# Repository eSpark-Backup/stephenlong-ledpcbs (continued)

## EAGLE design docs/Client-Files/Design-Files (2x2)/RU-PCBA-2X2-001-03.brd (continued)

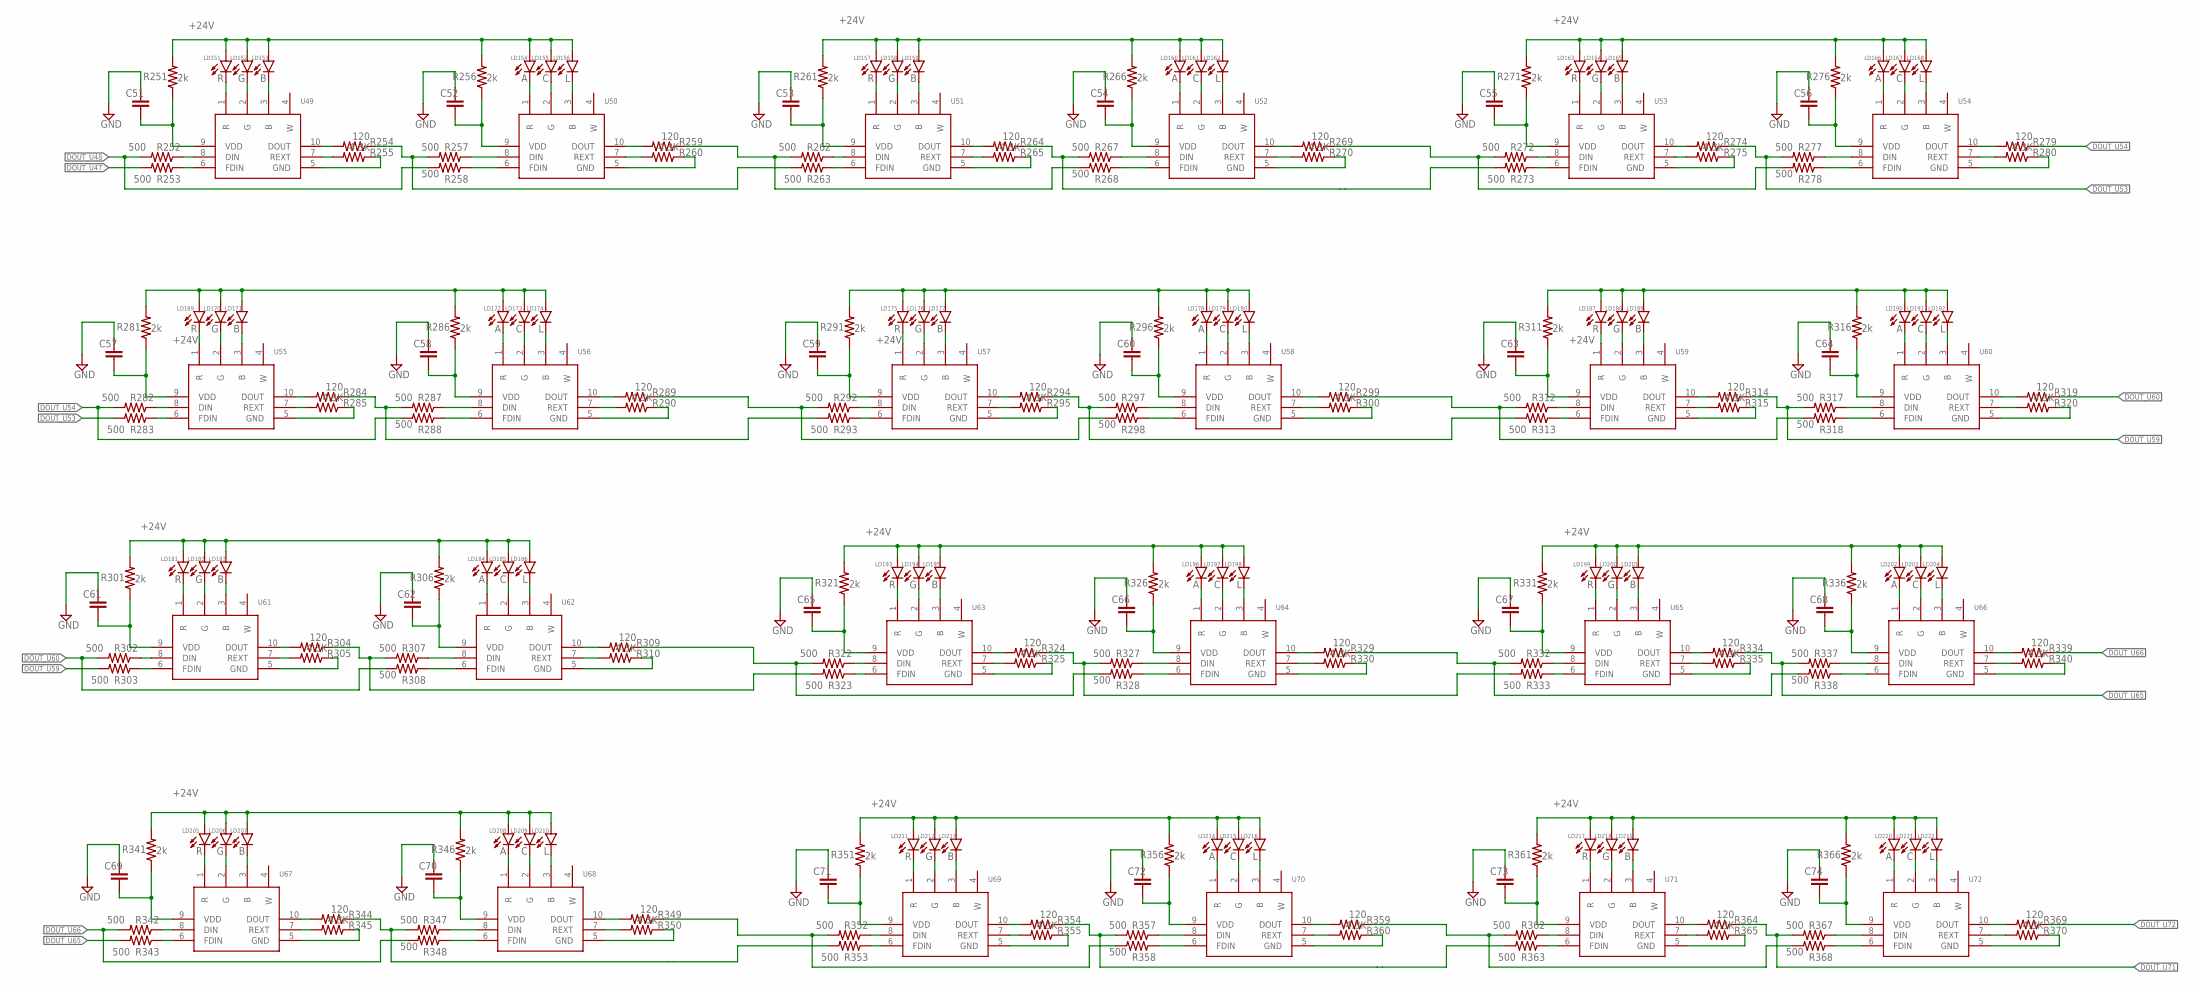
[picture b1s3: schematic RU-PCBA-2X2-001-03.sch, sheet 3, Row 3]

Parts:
C51, C52, C53, C54, C55, C56, C57, C58, C59, C60, C61, C62, C63, C64, C65, C66, C67, C68, C69, C70, C71, C72, C73, C74: C-EUC1206; C1206; MPN C_104
LD151, LD157, LD163, LD169, LD175, LD181, LD187, LD193, LD199, LD205, LD211, LD217: R; 5050LED; MPN R_5050
LD152, LD158, LD164, LD170, LD176, LD182, LD188, LD194, LD200, LD206, LD212, LD218: G; 5050LED; MPN G_5050
LD153, LD159, LD165, LD171, LD177, LD183, LD189, LD195, LD201, LD207, LD213, LD219: B; 5050LED; MPN B_5050
LD154, LD160, LD166, LD172, LD178, LD184, LD190, LD196, LD202, LD208, LD214, LD220: A; 5050LED; MPN A_5050
LD155, LD161, LD167, LD173, LD179, LD185, LD191, LD197, LD203, LD209, LD215, LD221: C; 5050LED; MPN C_5050
LD156, LD162, LD168, LD174, LD180, LD186, LD192, LD198, LD204, LD210, LD216, LD222: L; 5050LED; MPN L_5050
R251, R256, R261, R266, R271, R276, R281, R286, R291, R296, R301, R306, R311, R316, R321, R326, R331, R336, R341, R346, R351, R356, R361, R366: 2k; R1206; MPN R_VDD
R252, R253, R257, R258, R262, R263, R267, R268, R272, R273, R277, R278, R282, R283, R287, R288, R292, R293, R297, R298, R302, R303, R307, R308, R312, R313, R317, R318, R322, R323, R327, R328, R332, R333, R337, R338, R342, R343, R347, R348, R352, R353, R357, R358, R362, R363, R367, R368: 500; R0805; MPN R_500
R254, R259, R264, R269, R274, R279, R284, R289, R294, R299, R304, R309, R314, R319, R324, R329, R334, R339, R344, R349, R354, R359, R364, R369: 120; R0805; MPN R_120
R255, R260, R265, R270, R275, R280, R285, R290, R295, R300, R305, R310, R315, R320, R325, R330, R335, R340, R345, R350, R355, R360, R365, R370: 4.3K; R0805; MPN R_EXT
U49, U50, U51, U52, U53, U54, U55, U56, U57, U58, U59, U60, U61, U62, U63, U64, U65, U66, U67, U68, U69, U70, U71, U72: UCS7604; SOP100P600X175-10N; MPN UCS7604

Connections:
+24V: LD151.A, LD152.A, LD153.A, LD154.A, LD155.A, LD156.A, LD157.A, LD158.A, LD159.A, LD160.A, LD161.A, LD162.A, LD163.A, LD164.A, LD165.A, LD166.A, LD167.A, LD168.A, LD169.A, LD170.A, LD171.A, LD172.A, LD173.A, LD174.A, LD175.A, LD176.A, LD177.A, LD178.A, LD179.A, LD180.A, LD181.A, LD182.A, LD183.A, LD184.A, LD185.A, LD186.A, LD187.A, LD188.A, LD189.A, LD190.A, LD191.A, LD192.A, LD193.A, LD194.A, LD195.A, LD196.A, LD197.A, LD198.A, LD199.A, LD200.A, LD201.A, LD202.A, LD203.A, LD204.A, LD205.A, LD206.A, LD207.A, LD208.A, LD209.A, LD210.A, LD211.A, LD212.A, LD213.A, LD214.A, LD215.A, LD216.A, LD217.A, LD218.A, LD219.A, LD220.A, LD221.A, LD222.A, R251.2, R256.2, R261.2, R266.2, R271.2, R276.2, R281.2, R286.2, R291.2, R296.2, R301.2, R306.2, R311.2, R316.2, R321.2, R326.2, R331.2, R336.2, R341.2, R346.2, R351.2, R356.2, R361.2, R366.2; also elsewhere on the board
DOUT_U47: R253.2; also elsewhere on the board
DOUT_U48: R252.2, R258.2; also elsewhere on the board
DOUT_U53: R274.1, R277.2, R283.2
DOUT_U54: R279.1, R282.2, R288.2
DOUT_U59: R303.2, R314.1, R317.2
DOUT_U60: R302.2, R308.2, R319.1
DOUT_U65: R334.1, R337.2, R343.2
DOUT_U66: R339.1, R342.2, R348.2
DOUT_U71: R364.1, R367.2; also elsewhere on the board
DOUT_U72: R369.1; also elsewhere on the board
GND: C51.2, C52.2, C53.2, C54.2, C55.2, C56.2, C57.2, C58.2, C59.2, C60.2, C61.2, C62.2, C63.2, C64.2, C65.2, C66.2, C67.2, C68.2, C69.2, C70.2, C71.2, C72.2, C73.2, C74.2, R255.1, R260.1, R265.1, R270.1, R275.1, R280.1, R285.1, R290.1, R295.1, R300.1, R305.1, R310.1, R315.1, R320.1, R325.1, R330.1, R335.1, R340.1, R345.1, R350.1, R355.1, R360.1, R365.1, R370.1, U49.5 (GND), U50.5 (GND), U51.5 (GND), U52.5 (GND), U53.5 (GND), U54.5 (GND), U55.5 (GND), U56.5 (GND), U57.5 (GND), U58.5 (GND), U59.5 (GND), U60.5 (GND), U61.5 (GND), U62.5 (GND), U63.5 (GND), U64.5 (GND), U65.5 (GND), U66.5 (GND), U67.5 (GND), U68.5 (GND), U69.5 (GND), U70.5 (GND), U71.5 (GND), U72.5 (GND); also elsewhere on the board
unnamed: C51.1, R251.1, U49.9 (VDD)
unnamed: LD151.K (C), U49.1 (R)
unnamed: LD152.K (C), U49.2 (G)
unnamed: LD153.K (C), U49.3 (B)
unnamed: R252.1, U49.8 (DIN)
unnamed: R253.1, U49.6 (FDIN)
unnamed: R254.2, U49.10 (DOUT)
unnamed: R255.2, U49.7 (REXT)
unnamed: LD154.K (C), U50.1 (R)
unnamed: LD155.K (C), U50.2 (G)
unnamed: LD156.K (C), U50.3 (B)
unnamed: C52.1, R256.1, U50.9 (VDD)
unnamed: R257.1, U50.8 (DIN)
unnamed: R258.1, U50.6 (FDIN)
unnamed: R259.2, U50.10 (DOUT)
unnamed: R260.2, U50.7 (REXT)
unnamed: R259.1, R262.2, R268.2
unnamed: C53.1, R261.1, U51.9 (VDD)
unnamed: LD157.K (C), U51.1 (R)
unnamed: LD158.K (C), U51.2 (G)
unnamed: LD159.K (C), U51.3 (B)
unnamed: R262.1, U51.8 (DIN)
unnamed: R263.1, U51.6 (FDIN)
unnamed: R264.2, U51.10 (DOUT)
unnamed: R265.2, U51.7 (REXT)
unnamed: LD160.K (C), U52.1 (R)
unnamed: LD161.K (C), U52.2 (G)
unnamed: LD162.K (C), U52.3 (B)
unnamed: C54.1, R266.1, U52.9 (VDD)
unnamed: R267.1, U52.8 (DIN)
unnamed: R268.1, U52.6 (FDIN)
unnamed: R254.1, R257.2, R263.2
unnamed: R269.2, U52.10 (DOUT)
unnamed: R270.2, U52.7 (REXT)
unnamed: R269.1, R272.2, R278.2
unnamed: C55.1, R271.1, U53.9 (VDD)
unnamed: LD163.K (C), U53.1 (R)
unnamed: LD164.K (C), U53.2 (G)
unnamed: LD165.K (C), U53.3 (B)
unnamed: R272.1, U53.8 (DIN)
unnamed: R273.1, U53.6 (FDIN)
unnamed: R274.2, U53.10 (DOUT)
unnamed: R275.2, U53.7 (REXT)
unnamed: LD166.K (C), U54.1 (R)
unnamed: LD167.K (C), U54.2 (G)
unnamed: LD168.K (C), U54.3 (B)
unnamed: C56.1, R276.1, U54.9 (VDD)
unnamed: R277.1, U54.8 (DIN)
unnamed: R278.1, U54.6 (FDIN)
unnamed: R264.1, R267.2, R273.2
unnamed: R279.2, U54.10 (DOUT)
unnamed: R280.2, U54.7 (REXT)
unnamed: C57.1, R281.1, U55.9 (VDD)
unnamed: LD169.K (C), U55.1 (R)
unnamed: LD170.K (C), U55.2 (G)
unnamed: LD171.K (C), U55.3 (B)
unnamed: R282.1, U55.8 (DIN)
unnamed: R283.1, U55.6 (FDIN)
unnamed: R284.2, U55.10 (DOUT)
unnamed: R285.2, U55.7 (REXT)
unnamed: LD172.K (C), U56.1 (R)
unnamed: LD173.K (C), U56.2 (G)
unnamed: LD174.K (C), U56.3 (B)
unnamed: C58.1, R286.1, U56.9 (VDD)
unnamed: R287.1, U56.8 (DIN)
unnamed: R284.1, R287.2, R293.2
unnamed: R288.1, U56.6 (FDIN)
unnamed: R289.2, U56.10 (DOUT)
unnamed: R290.2, U56.7 (REXT)
unnamed: R289.1, R292.2, R298.2
unnamed: C59.1, R291.1, U57.9 (VDD)
unnamed: LD175.K (C), U57.1 (R)
unnamed: LD176.K (C), U57.2 (G)
unnamed: LD177.K (C), U57.3 (B)
unnamed: R292.1, U57.8 (DIN)
unnamed: R293.1, U57.6 (FDIN)
unnamed: R294.2, U57.10 (DOUT)
unnamed: R295.2, U57.7 (REXT)
unnamed: LD178.K (C), U58.1 (R)
unnamed: LD179.K (C), U58.2 (G)
unnamed: LD180.K (C), U58.3 (B)
unnamed: C60.1, R296.1, U58.9 (VDD)
unnamed: R297.1, U58.8 (DIN)
unnamed: R294.1, R297.2, R313.2
unnamed: R298.1, U58.6 (FDIN)
unnamed: R299.2, U58.10 (DOUT)
unnamed: R300.2, U58.7 (REXT)
unnamed: R299.1, R312.2, R318.2
unnamed: C61.1, R301.1, U61.9 (VDD)
unnamed: LD181.K (C), U61.1 (R)
unnamed: LD182.K (C), U61.2 (G)
unnamed: LD183.K (C), U61.3 (B)
unnamed: R302.1, U61.8 (DIN)
unnamed: R303.1, U61.6 (FDIN)
unnamed: R304.2, U61.10 (DOUT)
unnamed: R305.2, U61.7 (REXT)
unnamed: LD184.K (C), U62.1 (R)
unnamed: LD185.K (C), U62.2 (G)
unnamed: LD186.K (C), U62.3 (B)
unnamed: C62.1, R306.1, U62.9 (VDD)
unnamed: R307.1, U62.8 (DIN)
unnamed: R308.1, U62.6 (FDIN)
unnamed: R309.2, U62.10 (DOUT)
unnamed: R310.2, U62.7 (REXT)
unnamed: R309.1, R322.2, R328.2
unnamed: C63.1, R311.1, U59.9 (VDD)
unnamed: LD187.K (C), U59.1 (R)
unnamed: LD188.K (C), U59.2 (G)
unnamed: LD189.K (C), U59.3 (B)
unnamed: R312.1, U59.8 (DIN)
unnamed: R313.1, U59.6 (FDIN)
unnamed: R314.2, U59.10 (DOUT)
unnamed: R315.2, U59.7 (REXT)
unnamed: LD190.K (C), U60.1 (R)
unnamed: LD191.K (C), U60.2 (G)
unnamed: LD192.K (C), U60.3 (B)
unnamed: C64.1, R316.1, U60.9 (VDD)
unnamed: R317.1, U60.8 (DIN)
unnamed: R318.1, U60.6 (FDIN)
unnamed: R319.2, U60.10 (DOUT)
unnamed: R320.2, U60.7 (REXT)
unnamed: C65.1, R321.1, U63.9 (VDD)
unnamed: LD193.K (C), U63.1 (R)
unnamed: LD194.K (C), U63.2 (G)
unnamed: LD195.K (C), U63.3 (B)
unnamed: R322.1, U63.8 (DIN)
unnamed: R323.1, U63.6 (FDIN)
unnamed: R324.2, U63.10 (DOUT)
unnamed: R325.2, U63.7 (REXT)
unnamed: LD196.K (C), U64.1 (R)
unnamed: LD197.K (C), U64.2 (G)
unnamed: LD198.K (C), U64.3 (B)
unnamed: C66.1, R326.1, U64.9 (VDD)
unnamed: R327.1, U64.8 (DIN)
unnamed: R328.1, U64.6 (FDIN)
unnamed: R304.1, R307.2, R323.2
unnamed: R329.2, U64.10 (DOUT)
unnamed: R330.2, U64.7 (REXT)
unnamed: R329.1, R332.2, R338.2
unnamed: C67.1, R331.1, U65.9 (VDD)
unnamed: LD199.K (C), U65.1 (R)
unnamed: LD200.K (C), U65.2 (G)
unnamed: LD201.K (C), U65.3 (B)
unnamed: R332.1, U65.8 (DIN)
unnamed: R333.1, U65.6 (FDIN)
unnamed: R334.2, U65.10 (DOUT)
unnamed: R335.2, U65.7 (REXT)
unnamed: LD202.K (C), U66.1 (R)
unnamed: LD203.K (C), U66.2 (G)
unnamed: LD204.K (C), U66.3 (B)
unnamed: C68.1, R336.1, U66.9 (VDD)
unnamed: R337.1, U66.8 (DIN)
unnamed: R338.1, U66.6 (FDIN)
unnamed: R324.1, R327.2, R333.2
unnamed: R339.2, U66.10 (DOUT)
unnamed: R340.2, U66.7 (REXT)
unnamed: C69.1, R341.1, U67.9 (VDD)
unnamed: LD205.K (C), U67.1 (R)
unnamed: LD206.K (C), U67.2 (G)
unnamed: LD207.K (C), U67.3 (B)
unnamed: R342.1, U67.8 (DIN)
unnamed: R343.1, U67.6 (FDIN)
unnamed: R344.2, U67.10 (DOUT)
unnamed: R345.2, U67.7 (REXT)
unnamed: LD208.K (C), U68.1 (R)
unnamed: LD209.K (C), U68.2 (G)
unnamed: LD210.K (C), U68.3 (B)
unnamed: C70.1, R346.1, U68.9 (VDD)
unnamed: R347.1, U68.8 (DIN)
unnamed: R348.1, U68.6 (FDIN)
unnamed: R349.2, U68.10 (DOUT)
unnamed: R350.2, U68.7 (REXT)
unnamed: R349.1, R352.2, R358.2
unnamed: C71.1, R351.1, U69.9 (VDD)
unnamed: LD211.K (C), U69.1 (R)
unnamed: LD212.K (C), U69.2 (G)
unnamed: LD213.K (C), U69.3 (B)
unnamed: R352.1, U69.8 (DIN)
unnamed: R353.1, U69.6 (FDIN)
unnamed: R354.2, U69.10 (DOUT)
unnamed: R355.2, U69.7 (REXT)
unnamed: LD214.K (C), U70.1 (R)
unnamed: LD215.K (C), U70.2 (G)
unnamed: LD216.K (C), U70.3 (B)
unnamed: C72.1, R356.1, U70.9 (VDD)
unnamed: R357.1, U70.8 (DIN)
unnamed: R358.1, U70.6 (FDIN)
unnamed: R344.1, R347.2, R353.2
unnamed: R359.2, U70.10 (DOUT)
unnamed: R360.2, U70.7 (REXT)
unnamed: R359.1, R362.2, R368.2
unnamed: C73.1, R361.1, U71.9 (VDD)
unnamed: LD217.K (C), U71.1 (R)
unnamed: LD218.K (C), U71.2 (G)
unnamed: LD219.K (C), U71.3 (B)
unnamed: R362.1, U71.8 (DIN)
unnamed: R363.1, U71.6 (FDIN)
unnamed: R364.2, U71.10 (DOUT)
unnamed: R365.2, U71.7 (REXT)
unnamed: LD220.K (C), U72.1 (R)
unnamed: LD221.K (C), U72.2 (G)
unnamed: LD222.K (C), U72.3 (B)
unnamed: C74.1, R366.1, U72.9 (VDD)
unnamed: R367.1, U72.8 (DIN)
unnamed: R368.1, U72.6 (FDIN)
unnamed: R354.1, R357.2, R363.2
unnamed: R369.2, U72.10 (DOUT)
unnamed: R370.2, U72.7 (REXT)

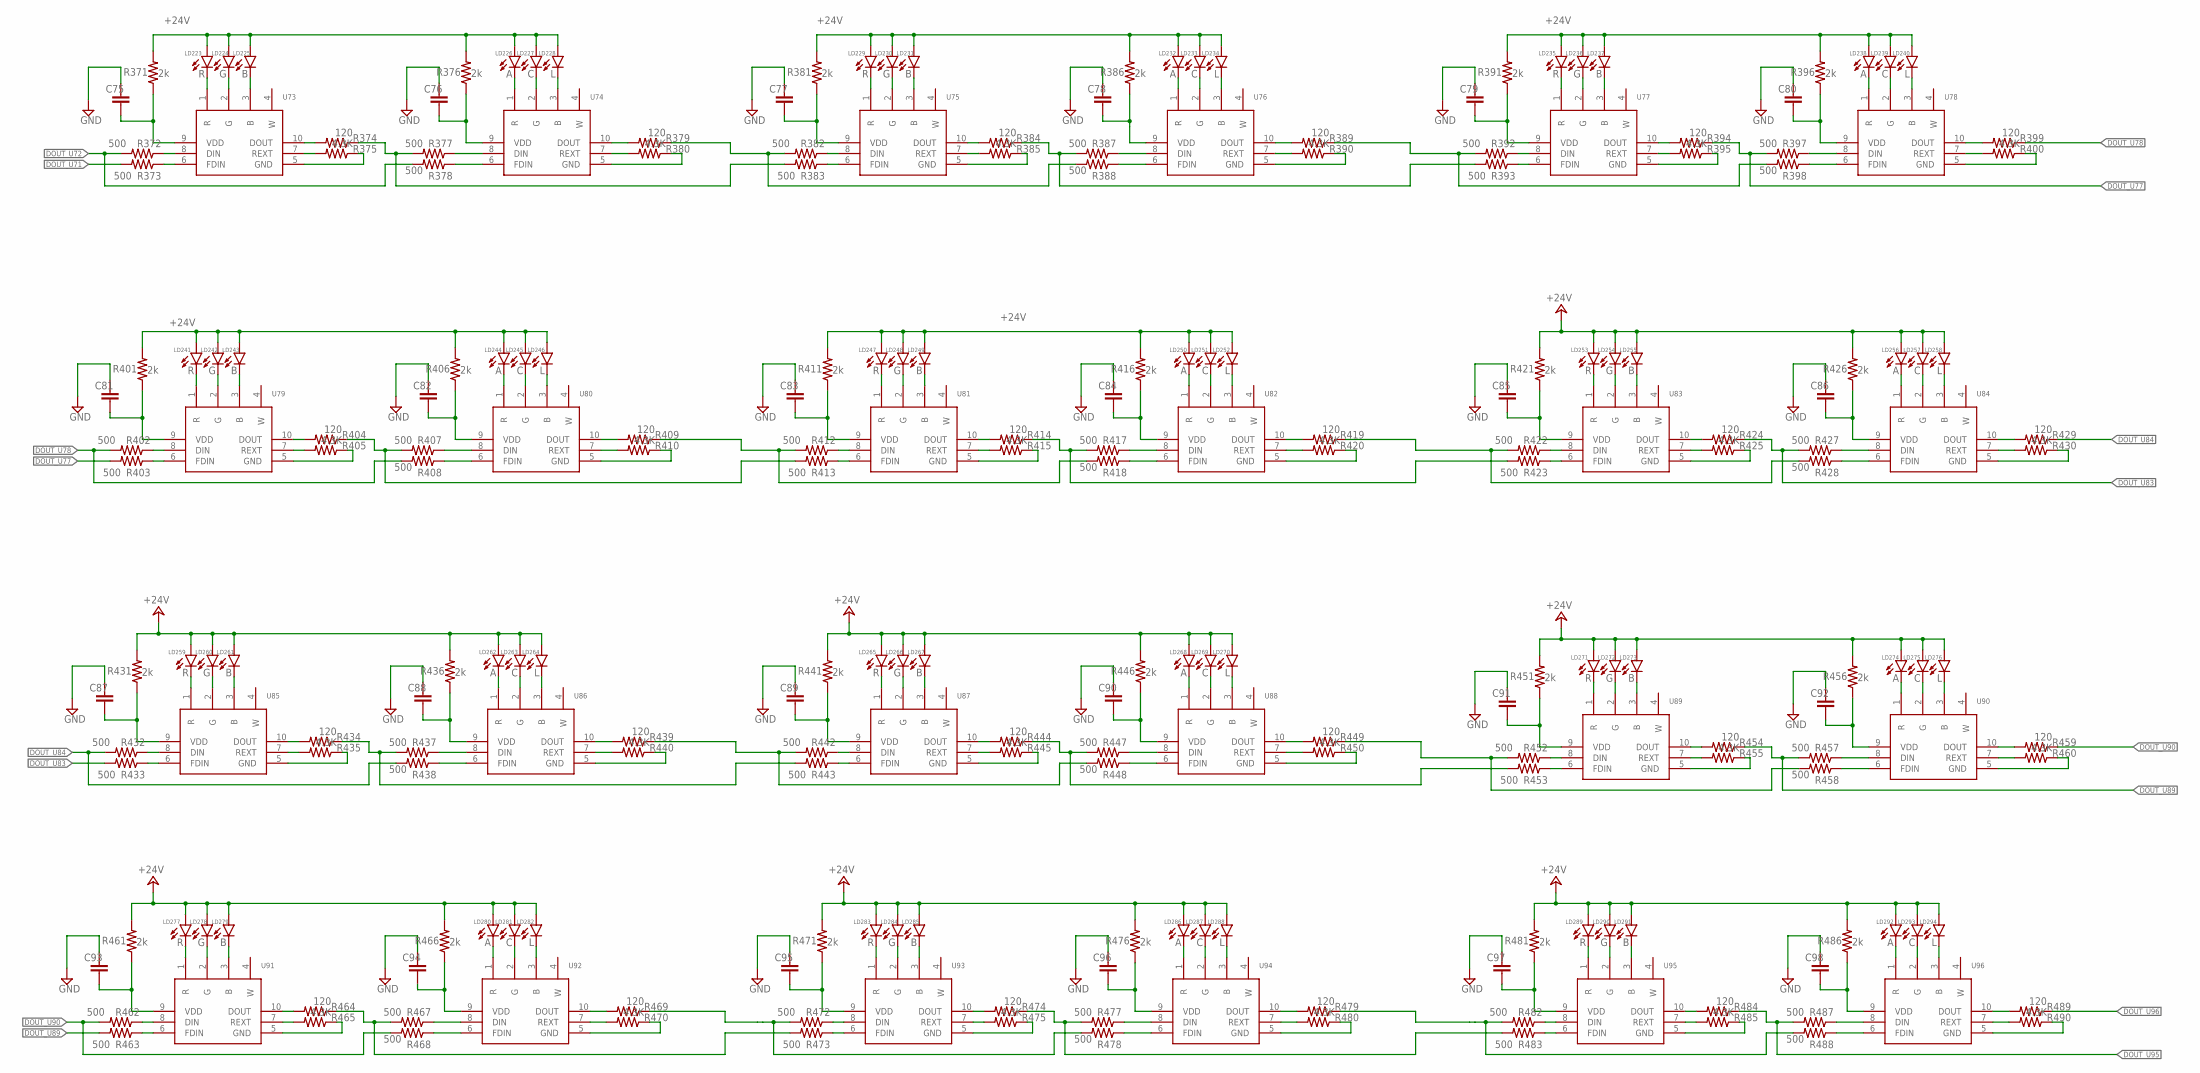
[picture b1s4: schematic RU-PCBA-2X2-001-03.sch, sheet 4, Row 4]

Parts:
C75, C76, C77, C78, C79, C80, C81, C82, C83, C84, C85, C86, C87, C88, C89, C90, C91, C92, C93, C94, C95, C96, C97, C98: C-EUC1206; C1206; MPN C_104
LD223, LD229, LD235, LD241, LD247, LD253, LD259, LD265, LD271, LD277, LD283, LD289: R; 5050LED; MPN R_5050
LD224, LD230, LD236, LD242, LD248, LD254, LD260, LD266, LD272, LD278, LD284, LD290: G; 5050LED; MPN G_5050
LD225, LD231, LD237, LD243, LD249, LD255, LD261, LD267, LD273, LD279, LD285, LD291: B; 5050LED; MPN B_5050
LD226, LD232, LD238, LD244, LD250, LD256, LD262, LD268, LD274, LD280, LD286, LD292: A; 5050LED; MPN A_5050
LD227, LD233, LD239, LD245, LD251, LD257, LD263, LD269, LD275, LD281, LD287, LD293: C; 5050LED; MPN C_5050
LD228, LD234, LD240, LD246, LD252, LD258, LD264, LD270, LD276, LD282, LD288, LD294: L; 5050LED; MPN L_5050
R371, R376, R381, R386, R391, R396, R401, R406, R411, R416, R421, R426, R431, R436, R441, R446, R451, R456, R461, R466, R471, R476, R481, R486: 2k; R1206; MPN R_VDD
R372, R373, R377, R378, R382, R383, R387, R388, R392, R393, R397, R398, R402, R403, R407, R408, R412, R413, R417, R418, R422, R423, R427, R428, R432, R433, R437, R438, R442, R443, R447, R448, R452, R453, R457, R458, R462, R463, R467, R468, R472, R473, R477, R478, R482, R483, R487, R488: 500; R0805; MPN R_500
R374, R379, R384, R389, R394, R399, R404, R409, R414, R419, R424, R429, R434, R439, R444, R449, R454, R459, R464, R469, R474, R479, R484, R489: 120; R0805; MPN R_120
R375, R380, R385, R390, R395, R400, R405, R410, R415, R420, R425, R430, R435, R440, R445, R450, R455, R460, R465, R470, R475, R480, R485, R490: 4.3K; R0805; MPN R_EXT
U73, U74, U75, U76, U77, U78, U79, U80, U81, U82, U83, U84, U85, U86, U87, U88, U89, U90, U91, U92, U93, U94, U95, U96: UCS7604; SOP100P600X175-10N; MPN UCS7604

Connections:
+24V: LD223.A, LD224.A, LD225.A, LD226.A, LD227.A, LD228.A, LD229.A, LD230.A, LD231.A, LD232.A, LD233.A, LD234.A, LD235.A, LD236.A, LD237.A, LD238.A, LD239.A, LD240.A, LD241.A, LD242.A, LD243.A, LD244.A, LD245.A, LD246.A, LD247.A, LD248.A, LD249.A, LD250.A, LD251.A, LD252.A, LD253.A, LD254.A, LD255.A, LD256.A, LD257.A, LD258.A, LD259.A, LD260.A, LD261.A, LD262.A, LD263.A, LD264.A, LD265.A, LD266.A, LD267.A, LD268.A, LD269.A, LD270.A, LD271.A, LD272.A, LD273.A, LD274.A, LD275.A, LD276.A, LD277.A, LD278.A, LD279.A, LD280.A, LD281.A, LD282.A, LD283.A, LD284.A, LD285.A, LD286.A, LD287.A, LD288.A, LD289.A, LD290.A, LD291.A, LD292.A, LD293.A, LD294.A, R371.2, R376.2, R381.2, R386.2, R391.2, R396.2, R401.2, R406.2, R411.2, R416.2, R421.2, R426.2, R431.2, R436.2, R441.2, R446.2, R451.2, R456.2, R461.2, R466.2, R471.2, R476.2, R481.2, R486.2; also elsewhere on the board
DOUT_U71: R373.2; also elsewhere on the board
DOUT_U72: R372.2, R378.2; also elsewhere on the board
DOUT_U77: R394.1, R397.2, R403.2
DOUT_U78: R399.1, R402.2, R408.2
DOUT_U83: R424.1, R427.2, R433.2
DOUT_U84: R429.1, R432.2, R438.2
DOUT_U89: R454.1, R457.2, R463.2
DOUT_U90: R459.1, R462.2, R468.2
DOUT_U95: R484.1, R487.2; also elsewhere on the board
DOUT_U96: R489.1; also elsewhere on the board
GND: C75.2, C76.2, C77.2, C78.2, C79.2, C80.2, C81.2, C82.2, C83.2, C84.2, C85.2, C86.2, C87.2, C88.2, C89.2, C90.2, C91.2, C92.2, C93.2, C94.2, C95.2, C96.2, C97.2, C98.2, R375.1, R380.1, R385.1, R390.1, R395.1, R400.1, R405.1, R410.1, R415.1, R420.1, R425.1, R430.1, R435.1, R440.1, R445.1, R450.1, R455.1, R460.1, R465.1, R470.1, R475.1, R480.1, R485.1, R490.1, U73.5 (GND), U74.5 (GND), U75.5 (GND), U76.5 (GND), U77.5 (GND), U78.5 (GND), U79.5 (GND), U80.5 (GND), U81.5 (GND), U82.5 (GND), U83.5 (GND), U84.5 (GND), U85.5 (GND), U86.5 (GND), U87.5 (GND), U88.5 (GND), U89.5 (GND), U90.5 (GND), U91.5 (GND), U92.5 (GND), U93.5 (GND), U94.5 (GND), U95.5 (GND), U96.5 (GND); also elsewhere on the board
unnamed: C83.1, R411.1, U81.9 (VDD)
unnamed: LD247.K (C), U81.1 (R)
unnamed: C75.1, R371.1, U73.9 (VDD)
unnamed: LD223.K (C), U73.1 (R)
unnamed: LD224.K (C), U73.2 (G)
unnamed: LD225.K (C), U73.3 (B)
unnamed: R372.1, U73.8 (DIN)
unnamed: R373.1, U73.6 (FDIN)
unnamed: R374.2, U73.10 (DOUT)
unnamed: R375.2, U73.7 (REXT)
unnamed: LD226.K (C), U74.1 (R)
unnamed: LD227.K (C), U74.2 (G)
unnamed: LD228.K (C), U74.3 (B)
unnamed: C76.1, R376.1, U74.9 (VDD)
unnamed: R377.1, U74.8 (DIN)
unnamed: R378.1, U74.6 (FDIN)
unnamed: R379.2, U74.10 (DOUT)
unnamed: R380.2, U74.7 (REXT)
unnamed: R379.1, R382.2, R388.2
unnamed: LD248.K (C), U81.2 (G)
unnamed: C77.1, R381.1, U75.9 (VDD)
unnamed: LD229.K (C), U75.1 (R)
unnamed: LD230.K (C), U75.2 (G)
unnamed: LD231.K (C), U75.3 (B)
unnamed: R382.1, U75.8 (DIN)
unnamed: R383.1, U75.6 (FDIN)
unnamed: R384.2, U75.10 (DOUT)
unnamed: R385.2, U75.7 (REXT)
unnamed: LD232.K (C), U76.1 (R)
unnamed: LD233.K (C), U76.2 (G)
unnamed: LD234.K (C), U76.3 (B)
unnamed: C78.1, R386.1, U76.9 (VDD)
unnamed: R387.1, U76.8 (DIN)
unnamed: R388.1, U76.6 (FDIN)
unnamed: R374.1, R377.2, R383.2
unnamed: R389.2, U76.10 (DOUT)
unnamed: R390.2, U76.7 (REXT)
unnamed: R389.1, R392.2, R398.2
unnamed: LD249.K (C), U81.3 (B)
unnamed: C79.1, R391.1, U77.9 (VDD)
unnamed: LD235.K (C), U77.1 (R)
unnamed: LD236.K (C), U77.2 (G)
unnamed: LD237.K (C), U77.3 (B)
unnamed: R392.1, U77.8 (DIN)
unnamed: R393.1, U77.6 (FDIN)
unnamed: R394.2, U77.10 (DOUT)
unnamed: R395.2, U77.7 (REXT)
unnamed: LD238.K (C), U78.1 (R)
unnamed: LD239.K (C), U78.2 (G)
unnamed: LD240.K (C), U78.3 (B)
unnamed: C80.1, R396.1, U78.9 (VDD)
unnamed: R397.1, U78.8 (DIN)
unnamed: R398.1, U78.6 (FDIN)
unnamed: R384.1, R387.2, R393.2
unnamed: R399.2, U78.10 (DOUT)
unnamed: R400.2, U78.7 (REXT)
unnamed: R412.1, U81.8 (DIN)
unnamed: C81.1, R401.1, U79.9 (VDD)
unnamed: LD241.K (C), U79.1 (R)
unnamed: LD242.K (C), U79.2 (G)
unnamed: LD243.K (C), U79.3 (B)
unnamed: R402.1, U79.8 (DIN)
unnamed: R403.1, U79.6 (FDIN)
unnamed: R404.2, U79.10 (DOUT)
unnamed: R405.2, U79.7 (REXT)
unnamed: LD244.K (C), U80.1 (R)
unnamed: LD245.K (C), U80.2 (G)
unnamed: LD246.K (C), U80.3 (B)
unnamed: C82.1, R406.1, U80.9 (VDD)
unnamed: R407.1, U80.8 (DIN)
unnamed: R408.1, U80.6 (FDIN)
unnamed: R409.2, U80.10 (DOUT)
unnamed: R410.2, U80.7 (REXT)
unnamed: R409.1, R412.2, R418.2
unnamed: R413.1, U81.6 (FDIN)
unnamed: R414.2, U81.10 (DOUT)
unnamed: R415.2, U81.7 (REXT)
unnamed: LD250.K (C), U82.1 (R)
unnamed: LD251.K (C), U82.2 (G)
unnamed: LD252.K (C), U82.3 (B)
unnamed: C84.1, R416.1, U82.9 (VDD)
unnamed: R417.1, U82.8 (DIN)
unnamed: R418.1, U82.6 (FDIN)
unnamed: R404.1, R407.2, R413.2
unnamed: R419.2, U82.10 (DOUT)
unnamed: R420.2, U82.7 (REXT)
unnamed: R419.1, R422.2, R428.2
unnamed: C85.1, R421.1, U83.9 (VDD)
unnamed: LD253.K (C), U83.1 (R)
unnamed: LD254.K (C), U83.2 (G)
unnamed: LD255.K (C), U83.3 (B)
unnamed: R422.1, U83.8 (DIN)
unnamed: R423.1, U83.6 (FDIN)
unnamed: R424.2, U83.10 (DOUT)
unnamed: R425.2, U83.7 (REXT)
unnamed: LD256.K (C), U84.1 (R)
unnamed: LD257.K (C), U84.2 (G)
unnamed: LD258.K (C), U84.3 (B)
unnamed: C86.1, R426.1, U84.9 (VDD)
unnamed: R427.1, U84.8 (DIN)
unnamed: R428.1, U84.6 (FDIN)
unnamed: R414.1, R417.2, R423.2
unnamed: R429.2, U84.10 (DOUT)
unnamed: R430.2, U84.7 (REXT)
unnamed: C87.1, R431.1, U85.9 (VDD)
unnamed: LD259.K (C), U85.1 (R)
unnamed: LD260.K (C), U85.2 (G)
unnamed: LD261.K (C), U85.3 (B)
unnamed: R432.1, U85.8 (DIN)
unnamed: R433.1, U85.6 (FDIN)
unnamed: R434.2, U85.10 (DOUT)
unnamed: R435.2, U85.7 (REXT)
unnamed: LD262.K (C), U86.1 (R)
unnamed: LD263.K (C), U86.2 (G)
unnamed: LD264.K (C), U86.3 (B)
unnamed: C88.1, R436.1, U86.9 (VDD)
unnamed: R437.1, U86.8 (DIN)
unnamed: R438.1, U86.6 (FDIN)
unnamed: R439.2, U86.10 (DOUT)
unnamed: R440.2, U86.7 (REXT)
unnamed: R439.1, R442.2, R448.2
unnamed: C89.1, R441.1, U87.9 (VDD)
unnamed: LD265.K (C), U87.1 (R)
unnamed: LD266.K (C), U87.2 (G)
unnamed: LD267.K (C), U87.3 (B)
unnamed: R442.1, U87.8 (DIN)
unnamed: R443.1, U87.6 (FDIN)
unnamed: R444.2, U87.10 (DOUT)
unnamed: R445.2, U87.7 (REXT)
unnamed: LD268.K (C), U88.1 (R)
unnamed: LD269.K (C), U88.2 (G)
unnamed: LD270.K (C), U88.3 (B)
unnamed: C90.1, R446.1, U88.9 (VDD)
unnamed: R447.1, U88.8 (DIN)
unnamed: R448.1, U88.6 (FDIN)
unnamed: R434.1, R437.2, R443.2
unnamed: R449.2, U88.10 (DOUT)
unnamed: R450.2, U88.7 (REXT)
unnamed: R449.1, R452.2, R458.2
unnamed: C91.1, R451.1, U89.9 (VDD)
unnamed: LD271.K (C), U89.1 (R)
unnamed: LD272.K (C), U89.2 (G)
unnamed: LD273.K (C), U89.3 (B)
unnamed: R452.1, U89.8 (DIN)
unnamed: R453.1, U89.6 (FDIN)
unnamed: R454.2, U89.10 (DOUT)
unnamed: R455.2, U89.7 (REXT)
unnamed: LD274.K (C), U90.1 (R)
unnamed: LD275.K (C), U90.2 (G)
unnamed: LD276.K (C), U90.3 (B)
unnamed: C92.1, R456.1, U90.9 (VDD)
unnamed: R457.1, U90.8 (DIN)
unnamed: R458.1, U90.6 (FDIN)
unnamed: R444.1, R447.2, R453.2
unnamed: R459.2, U90.10 (DOUT)
unnamed: R460.2, U90.7 (REXT)
unnamed: C93.1, R461.1, U91.9 (VDD)
unnamed: LD277.K (C), U91.1 (R)
unnamed: LD278.K (C), U91.2 (G)
unnamed: LD279.K (C), U91.3 (B)
unnamed: R462.1, U91.8 (DIN)
unnamed: R463.1, U91.6 (FDIN)
unnamed: R464.2, U91.10 (DOUT)
unnamed: R465.2, U91.7 (REXT)
unnamed: LD280.K (C), U92.1 (R)
unnamed: LD281.K (C), U92.2 (G)
unnamed: LD282.K (C), U92.3 (B)
unnamed: C94.1, R466.1, U92.9 (VDD)
unnamed: R467.1, U92.8 (DIN)
unnamed: R468.1, U92.6 (FDIN)
unnamed: R469.2, U92.10 (DOUT)
unnamed: R470.2, U92.7 (REXT)
unnamed: R469.1, R472.2, R478.2
unnamed: C95.1, R471.1, U93.9 (VDD)
unnamed: LD283.K (C), U93.1 (R)
unnamed: LD284.K (C), U93.2 (G)
unnamed: LD285.K (C), U93.3 (B)
unnamed: R472.1, U93.8 (DIN)
unnamed: R473.1, U93.6 (FDIN)
unnamed: R474.2, U93.10 (DOUT)
unnamed: R475.2, U93.7 (REXT)
unnamed: LD286.K (C), U94.1 (R)
unnamed: LD287.K (C), U94.2 (G)
unnamed: LD288.K (C), U94.3 (B)
unnamed: C96.1, R476.1, U94.9 (VDD)
unnamed: R477.1, U94.8 (DIN)
unnamed: R474.1, R477.2, R483.2
unnamed: R478.1, U94.6 (FDIN)
unnamed: R464.1, R467.2, R473.2
unnamed: R479.2, U94.10 (DOUT)
unnamed: R480.2, U94.7 (REXT)
unnamed: R479.1, R482.2, R488.2
unnamed: C97.1, R481.1, U95.9 (VDD)
unnamed: LD289.K (C), U95.1 (R)
unnamed: LD290.K (C), U95.2 (G)
unnamed: LD291.K (C), U95.3 (B)
unnamed: R482.1, U95.8 (DIN)
unnamed: R483.1, U95.6 (FDIN)
unnamed: R484.2, U95.10 (DOUT)
unnamed: R485.2, U95.7 (REXT)
unnamed: LD292.K (C), U96.1 (R)
unnamed: LD293.K (C), U96.2 (G)
unnamed: LD294.K (C), U96.3 (B)
unnamed: C98.1, R486.1, U96.9 (VDD)
unnamed: R487.1, U96.8 (DIN)
unnamed: R488.1, U96.6 (FDIN)
unnamed: R489.2, U96.10 (DOUT)
unnamed: R490.2, U96.7 (REXT)
